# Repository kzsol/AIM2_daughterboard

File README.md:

# AIM2_daughterboard
## Overview:  
  
+ Design of an add-on microphone interface board for AIM-2, stackable through Mezzanine connectors  
+ KiCad v10.0  
+ Latest design version: v5  
  
## Contents:  
  
+ Schematic and PCB layout  
+ Custom design rules following PBCWay capabilities  
+ Custom symbol and footprint libraries  
  
## Quick Start:  
  
1. Clone and extract the entire project folder.  
2. [Install KiCad](https://www.kicad.org/download/) (version 10.0 or later is needed to open this project).  
3. Navigate to project's latest version folder and open `daughterboardv_.kicad_pro`.
4. On KiCad Project Manager, access the schematic and PCB by opening `daughterboardv_.kicad_sch` / `daughterboardv_.kicad_pcb` under Project Files tab, or click on `Schematic Editor` and `PCB Editor` on the right side.

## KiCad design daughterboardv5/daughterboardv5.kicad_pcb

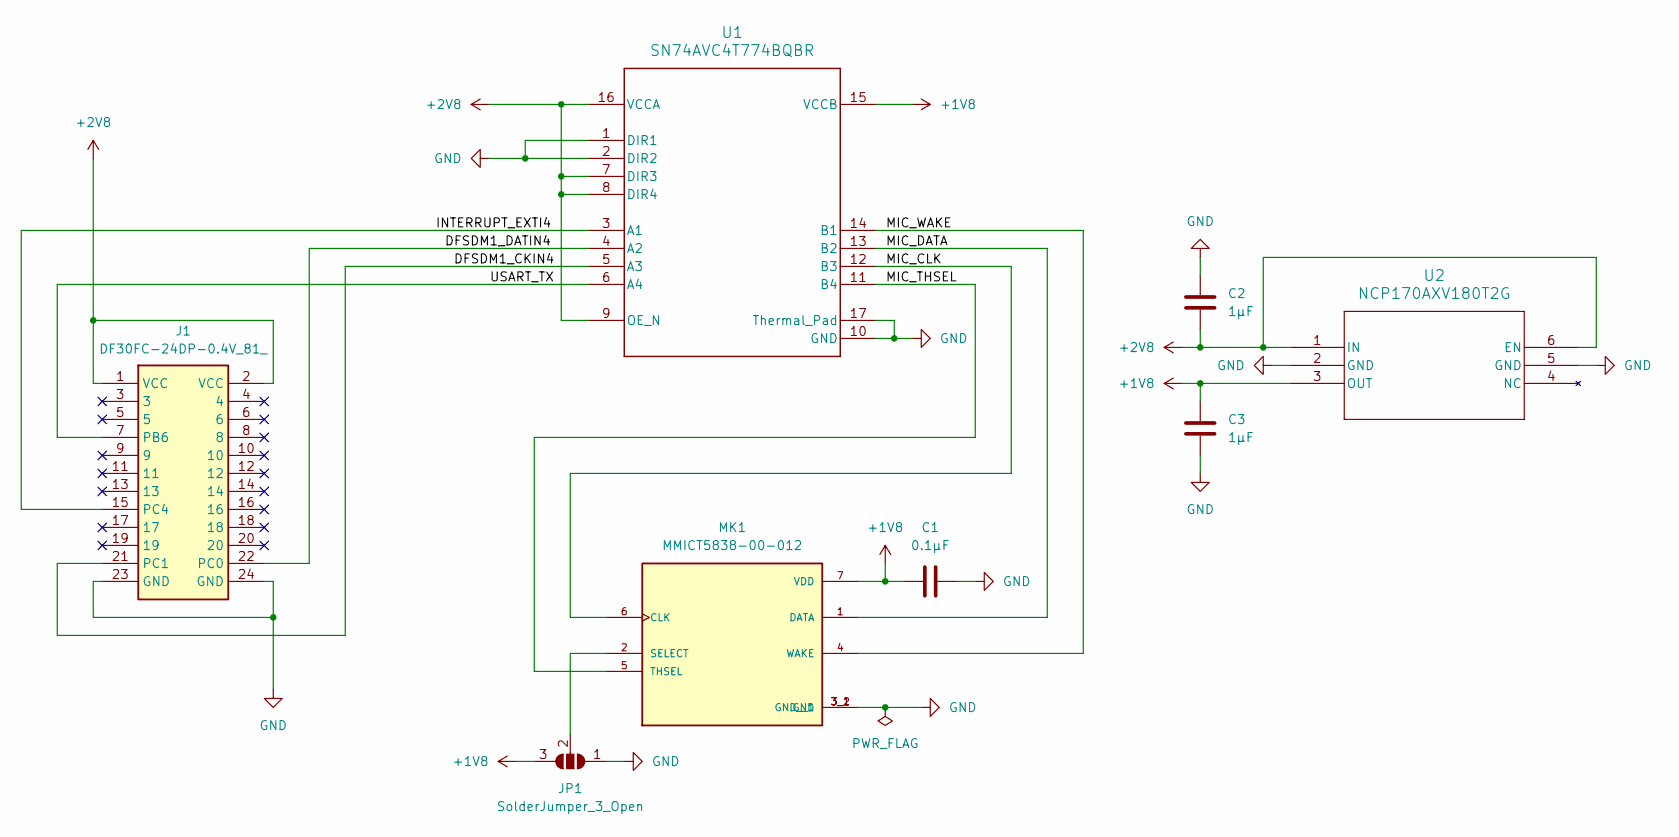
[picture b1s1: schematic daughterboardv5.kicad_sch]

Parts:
C1: 0.1µF; C_0201_0603Metric
C2, C3: 1µF; C_0201_0603Metric
J1: DF30FC-24DP-0.4V_81_; DF30FC24DP04V81; Mouser Part Number 798-DF30FC24DP04V81
JP1: SolderJumper_3_Open; SolderJumper-3_P1.3mm_Open_RoundedPad1.0x1.5mm
MK1: MMICT5838-00-012; MIC_MMICT5838-00-012; PARTREV 1.1
U1: SN74AVC4T774BQBR; BQB0016A-MFG
U2: NCP170AXV180T2G; SOT-563_1P3X1P7_ONS

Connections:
+1V8: C1.1, C3.1, JP1.3 (B), MK1.7 (VDD), U1.15 (VCCB), U2.3 (OUT)
+2V8: C2.1, J1.1 (VCC), J1.2 (VCC), U1.7 (DIR3), U1.8 (DIR4), U1.9 (OE_N), U1.16 (VCCA), U2.1 (IN), U2.6 (EN)
/DFSDM1_CKIN4: J1.21 (PC1), U1.5 (A3)
/DFSDM1_DATIN4: J1.22 (PC0), U1.4 (A2)
/INTERRUPT_EXTI4: J1.15 (PC4), U1.3 (A1)
/MIC_CLK: MK1.6 (CLK), U1.12 (B3)
/MIC_DATA: MK1.1 (DATA), U1.13 (B2)
/MIC_THSEL: MK1.5 (THSEL), U1.11 (B4)
/MIC_WAKE: MK1.4 (WAKE), U1.14 (B1)
/USART_TX: J1.7 (PB6), U1.6 (A4)
GND: C1.2, C2.2, C3.2, J1.23 (GND), J1.24 (GND), JP1.1 (A), MK1.3_1 (GND), MK1.3_2 (GND__1), U1.1 (DIR1), U1.2 (DIR2), U1.10 (GND), U1.17 (Thermal_Pad), U2.2 (GND), U2.5 (GND)
unnamed: JP1.2 (C), MK1.2 (SELECT)

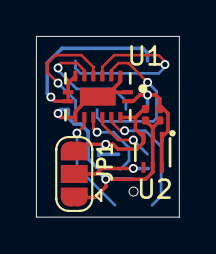
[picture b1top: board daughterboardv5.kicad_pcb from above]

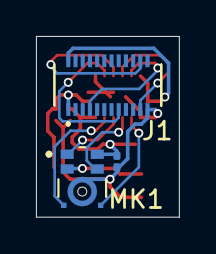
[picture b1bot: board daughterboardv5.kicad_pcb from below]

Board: 2 copper layers, 7.9 x 10.0 mm, 8 parts (3 on the bottom side), 12 nets.

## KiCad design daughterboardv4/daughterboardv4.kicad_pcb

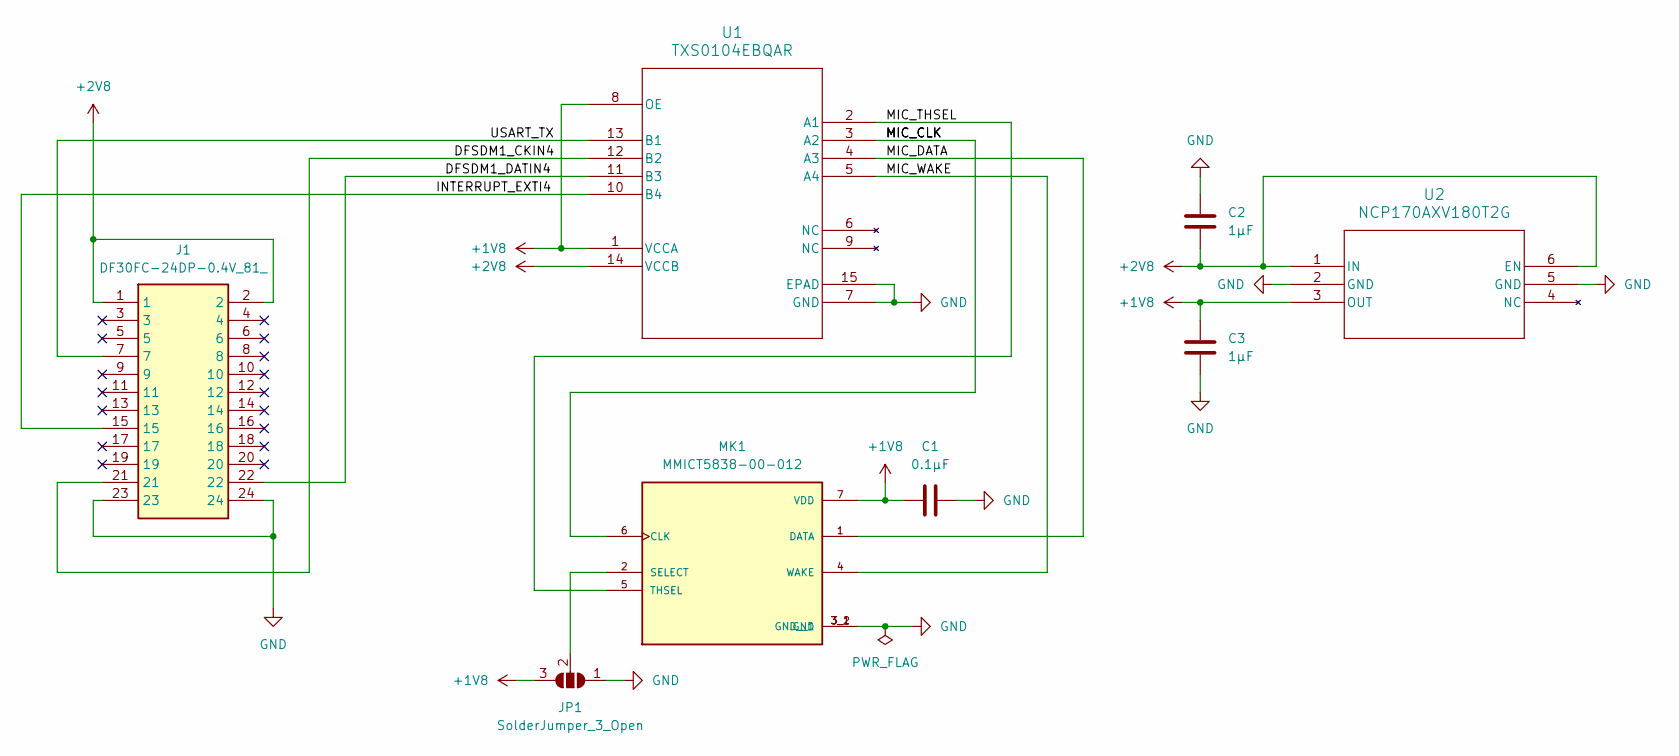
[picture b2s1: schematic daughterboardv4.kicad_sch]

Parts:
C1: 0.1µF; C_0201_0603Metric
C2, C3: 1µF; C_0201_0603Metric
J1: DF30FC-24DP-0.4V_81_; DF30FC24DP04V81; Mouser Part Number 798-DF30FC24DP04V81
JP1: SolderJumper_3_Open; SolderJumper-3_P1.3mm_Open_RoundedPad1.0x1.5mm
MK1: MMICT5838-00-012; MIC_MMICT5838-00-012; PARTREV 1.1
U1: TXS0104EBQAR; WQFN14_BQA_TEX
U2: NCP170AXV180T2G; SOT-563_1P3X1P7_ONS

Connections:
+1V8: C1.1, C3.1, JP1.3 (B), MK1.7 (VDD), U1.1 (VCCA), U1.8 (OE), U2.3 (OUT)
+2V8: C2.1, J1.1 (VCC), J1.2 (VCC), U1.14 (VCCB), U2.1 (IN), U2.6 (EN)
/DFSDM1_CKIN4: J1.21 (PC1), U1.12 (B2)
/DFSDM1_DATIN4: J1.22 (PC0), U1.11 (B3)
/INTERRUPT_EXTI4: J1.15 (PC4), U1.10 (B4)
/MIC_CLK: MK1.6 (CLK), U1.3 (A2)
/MIC_DATA: MK1.1 (DATA), U1.4 (A3)
/MIC_THSEL: MK1.5 (THSEL), U1.2 (A1)
/MIC_WAKE: MK1.4 (WAKE), U1.5 (A4)
/USART_TX: J1.7 (PB6), U1.13 (B1)
GND: C1.2, C2.2, C3.2, J1.23 (GND), J1.24 (GND), JP1.1 (A), MK1.3_1 (GND), MK1.3_2 (GND__1), U1.7 (GND), U1.15 (EPAD), U2.2 (GND), U2.5 (GND)
unnamed: JP1.2 (C), MK1.2 (SELECT)

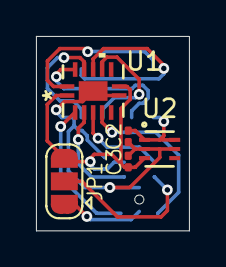
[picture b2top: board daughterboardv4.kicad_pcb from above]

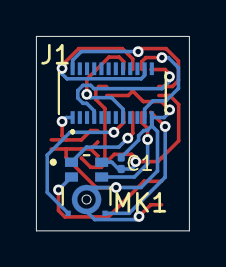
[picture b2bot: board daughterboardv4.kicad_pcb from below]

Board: 2 copper layers, 8.5 x 10.8 mm, 8 parts (3 on the bottom side), 12 nets.
